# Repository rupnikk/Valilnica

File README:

KALILNIK

Urban Rupnik
Zadlog 42, 5274 Črni Vrh
Start: 6. 6. 2016

Navodila za git:
git add . -Af
git commit -am "bla"

Verzija 1.1: 6. 6. 2016
Komentarji k shemi:
	LCD: 	- potenciometer za nastavljanje svetlosti, 
			- R/W = GND => se samo piše v spomin LCD-ja

	Izhodi:	- Luci:		-180 omski upor za nastavitev napetosti, ki 					mora biti na triacu in zagotovitev odprtja 						triaca.
						- 2.4 ohm + 0.2uF -> Snubber za optospojnik
						- 39 ohm + 0.05uF -> Snubber za induktivno breme
			- Grelec:	- brez Snubberjev zato ker je omsko breme

	Tipke: 	- paralelni upor -> pull-up upor (cca. 10k)
			- serijski upor -> ko je pin nastavljen kot vhod in je tipka pritisnjena (nizko stanje na vhodu) skozi tranzistor steče tok, ki je zaradi velike Ugs prevelik in lahko uniči pin. (cca. 220 ohm)

	Enkoder: - 10k pull-up upor, in 10k + 0.1uF C za filter

	MCU: 	- Potrebujemo najmanj 21 digitalnih I/O pinov => najmanjši tak je 32 pinski.
			- ne potrebujemo veliko spomina, niti procesorske moči, tako da bi se odločil za ATtiny88 NIMA možnosti za zunanji kristalni oscilator!!!!!!!!
		- Izbral sem ATMEGA32M1-AU

	Switcher: -http://si.farnell.com/infineon/ifx91041ej-v50/dc-dc-conv-buck-370khz-soic-8/dp/2432504

			- blokirni kondenzatorji cca. 2.2u in 100n

			- pi filter: (1/10*f0) f0=1/(2*pi*sqrt(L*C))

	konektorji: signalni: -jst xhp
			močnostni: 5.08 mm bom potem zbral

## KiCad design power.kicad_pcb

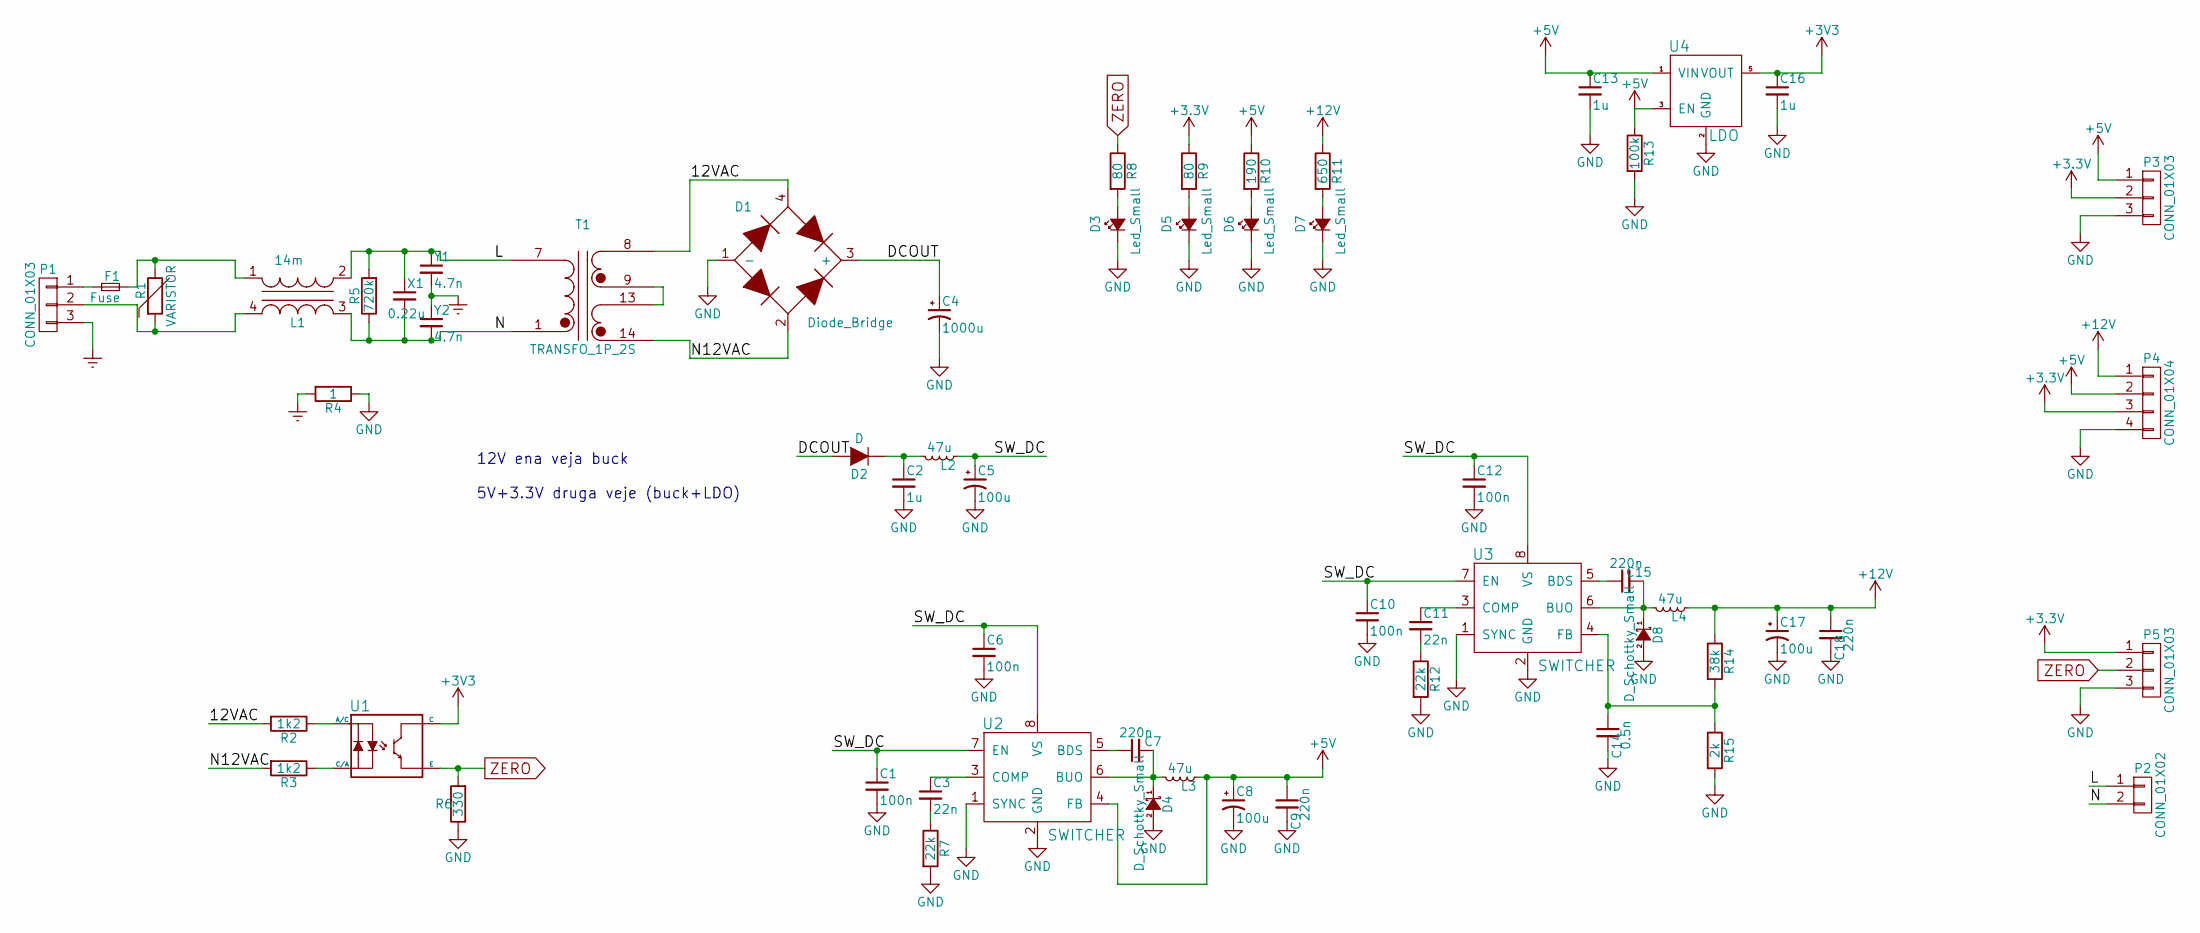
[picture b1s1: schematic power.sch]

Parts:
C1, C6, C10, C12: 100n; C_0603_HandSoldering
C2: 1u; R_0603_HandSoldering
C3, C11: 22n; C_0603_HandSoldering
C4: 1000u; C_13_21_5; Farnell number 9451323
C5, C8, C17: 100u; C_Radial_D6.3_L11.2_P2.5; Farnell number 9451080
C7, C9, C15, C18: 220n; C_0603_HandSoldering
C13, C16: 1u; C_0603_HandSoldering
C14: 0.5n; C_0603_HandSoldering
D1: Diode_Bridge; CIRC_BRIDGE_RECT
D2: D; SOD323F; Farnell number 1757770
D3: Led_Small; R_0603_HandSoldering; Farnell number 2463988
D4, D8: D_Schottky_Small; SOD323F; Farnell number 2575120
D5, D6, D7: Led_Small; R_0603_HandSoldering; Farnell number 2426215
F1: Fuse; Fuseholder_Fuse_5x20; Farnell number 1271632
L1: 14m; FILTER_SU9V; Farnell number 2364377
L2, L3, L4: 47u; TYS4018470M-10; Farnell number 2292522
P1: CONN_01X03; CONN_3x1x5.08; Farnell number 2008020
P2: CONN_01X02; CONN_2x1x5.08
P3, P5: CONN_01X03; CONN_3x1x2.54
P4: CONN_01X04; CONN_4x1x2.54
R1: VARISTOR; VARISTOR_MOV-14D431KTR; Farnell number 2250941
R2, R3: 1k2; CFR25; Farnell number 2329708
R4: 1; R_0805_HandSoldering
R5: 720k; CFR25; Farnell number 2329704
R6: 330; R_0603_HandSoldering
R7, R12: 22k; R_0603_HandSoldering
R8, R9: 80; R_0603_HandSoldering
R10: 190; R_0603_HandSoldering
R11: 650; R_0603_HandSoldering
R13: 100k; R_0603_HandSoldering
R14: 38k; R_0603_HandSoldering
R15: 2k; R_0603_HandSoldering
T1: TRANSFO_1P_2S; TRAFO_17_89_1314; Farnell number 1214618
U1: TRIAC_OPTOCOUPLER_2D+CE; SFH620-SMD_4pin; Farnell number 1469585
U2: SWITCHER; SOIC-8-N; Farnell number 2432504
U3: SWITCHER; SOIC-8-N; Farnell number 2480506
U4: LDO; SOT23-5; Farnell number 2363036
X1: 0.22u; X2_B32922; Farnell number 1112842
Y1, Y2: 4.7n; Y2_L20C7H; Farnell number 2576709

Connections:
+5V: C8.1, C9.1, C13.1, L3.1, P3.1, P4.2, R10.1, R13.1, U2.4 (FB), U4.1 (VIN), U4.3 (EN)
+12V: C17.1, C18.1, L4.1, P4.1, R11.1, R14.1
/12VAC: D1.4, R2.2, T1.8 (SB)
/DCOUT: C4.1, D1.3 (+), D2.2 (A)
/L: L1.2 (AB), P2.1, R5.2, T1.7 (AA), X1.1, Y1.1
/N: L1.3 (SA), P2.2, R5.1, T1.1 (AB), X1.2, Y2.2
/N12VAC: D1.2, R3.2, T1.14 (SC)
/SW_DC: C1.1, C5.1, C6.1, C10.1, C12.1, L2.1, U2.7 (EN), U2.8 (VS), U3.7 (EN), U3.8 (VS)
Earth: P1.3, R4.2, Y1.2, Y2.1
GND: C1.2, C2.2, C4.2, C5.2, C6.2, C8.2, C9.2, C10.2, C12.2, C13.2, C14.2, C16.2, C17.2, C18.2, D1.1 (-), D3.1 (K), D4.2 (A), D5.1 (K), D6.1 (K), D7.1 (K), D8.2 (A), P3.3, P4.4, P5.3, R4.1, R6.1, R7.2, R12.2, R13.2, R15.2, U2.1 (SYNC), U2.2 (GND), U3.1 (SYNC), U3.2 (GND), U4.2 (GND)
unnamed: C2.1, D2.1 (K), L2.2
unnamed: C3.1, U2.3 (COMP)
unnamed: C3.2, R7.1
unnamed: C7.1, U2.5 (BDS)
unnamed: C7.2, D4.1 (K), L3.2, U2.6 (BUO)
unnamed: C11.1, U3.3 (COMP)
unnamed: C11.2, R12.1
unnamed: C14.1, R14.2, R15.1, U3.4 (FB)
unnamed: C15.1, U3.5 (BDS)
unnamed: C15.2, D8.1 (K), L4.2, U3.6 (BUO)
unnamed: D3.2 (A), R8.2
unnamed: D5.2 (A), R9.2
unnamed: D6.2 (A), R10.2
unnamed: D7.2 (A), R11.2
unnamed: F1.1, P1.1
unnamed: F1.2, L1.1 (AA), R1.1
unnamed: L1.4 (SB), P1.2, R1.2
unnamed: R2.1, U1.1 (A/C)
unnamed: R3.1, U1.2 (C/A)
unnamed: T1.9 (SA), T1.13 (SD)
ZERO: P5.2, R6.2, R8.1, U1.3 (E)

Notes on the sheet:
12V ena veja buck 5V+3.3V druga veje (buck+LDO)

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
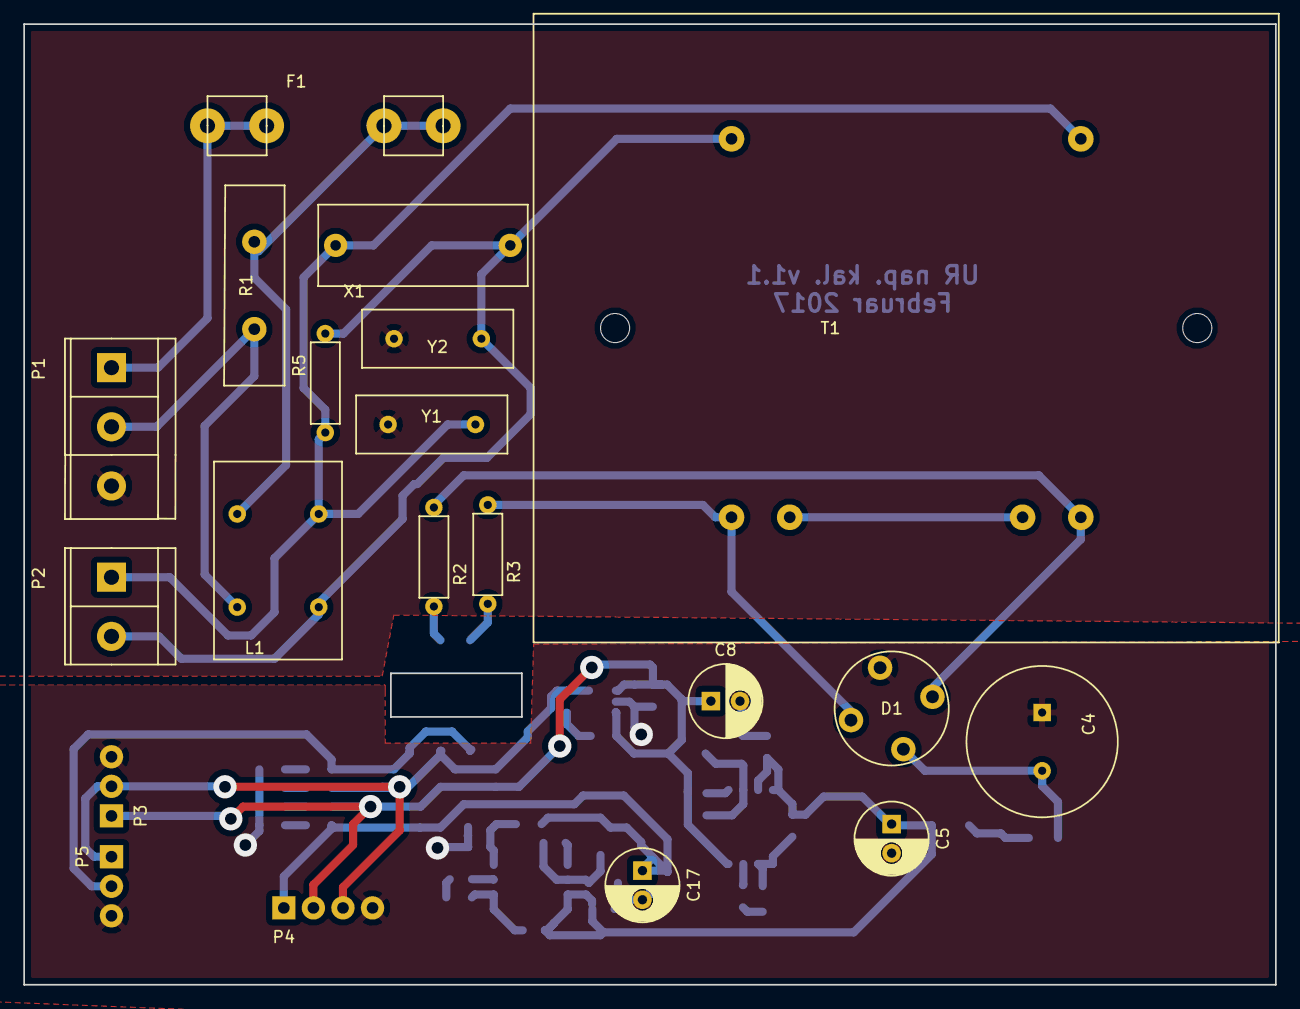
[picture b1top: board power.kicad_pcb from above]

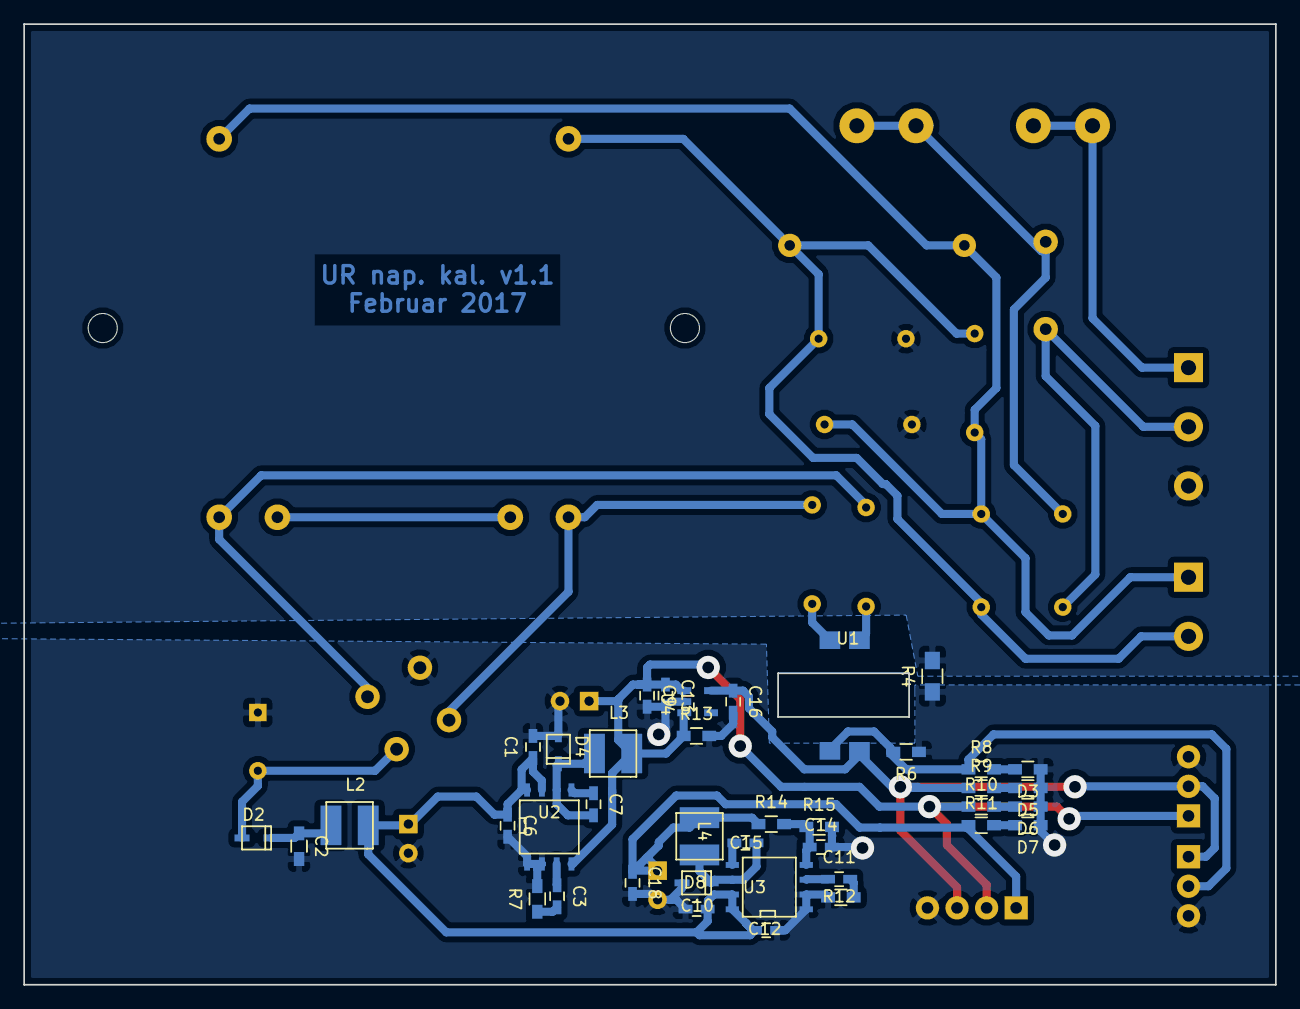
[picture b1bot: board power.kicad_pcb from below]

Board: 2 copper layers, 107.5 x 82.5 mm, 59 parts (39 on the bottom side), 32 nets.

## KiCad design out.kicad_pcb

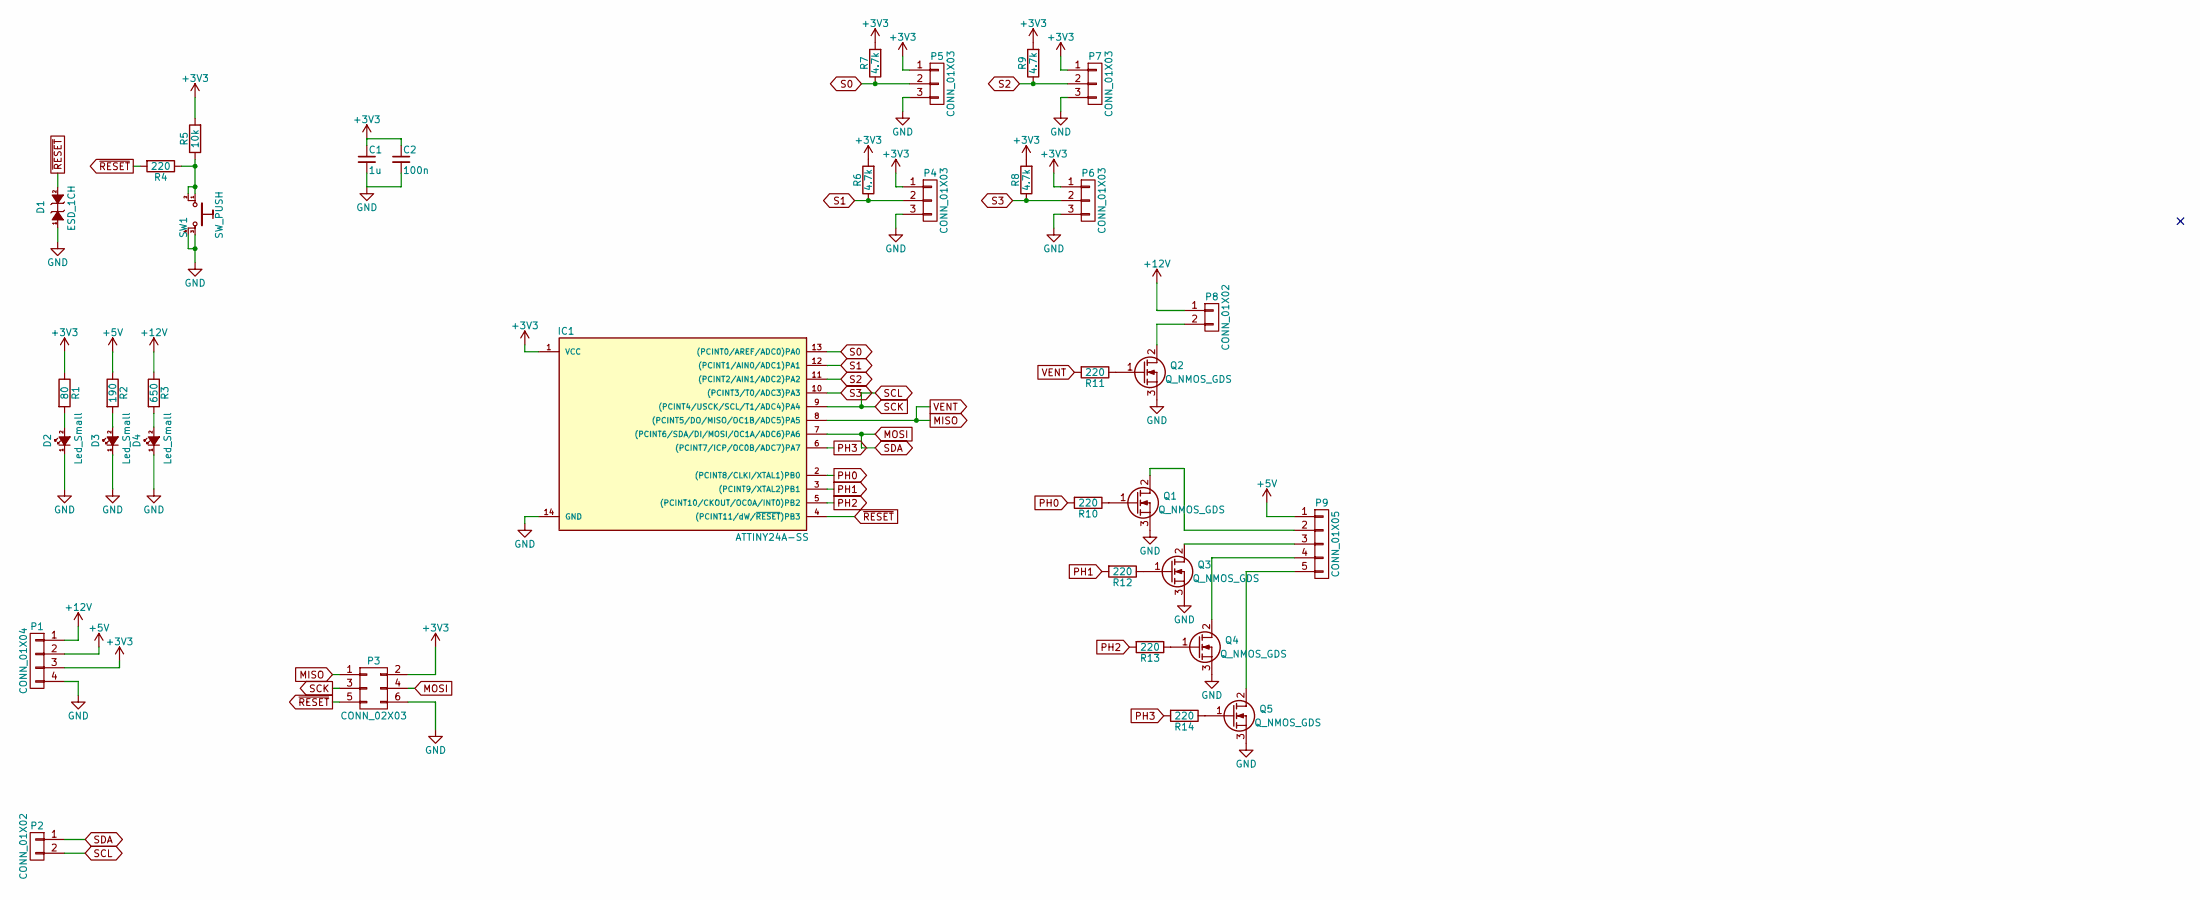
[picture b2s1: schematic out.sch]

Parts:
C1: 1u; C_0603_HandSoldering
C2: 100n; C_0603_HandSoldering
D1: ESD_1CH; SOD323F; Farnell number 8737517
D2, D3, D4: Led_Small; R_0603_HandSoldering
IC1: ATTINY24A-SS; SOIC-14_3.9x8.7mm_Pitch1.27mm
P1: CONN_01X04; CONN_4x1x2.54
P2: CONN_01X02; CONN_2x1x2.54
P3: CONN_02X03; IDC_Header_Straight_6pins
P4, P5, P6, P7: CONN_01X03; CONN_3x1x2.54
P8: CONN_01X02; CONN_2x1x5.08
P9: CONN_01X05; CONN_5x1x2.54
Q1, Q2, Q3, Q4, Q5: Q_NMOS_GDS; SOT89-3_Housing_Handsoldering_123; Farnell number 1834055
R1: 80; R_0603_HandSoldering
R2: 190; R_0603_HandSoldering
R3: 650; R_0603_HandSoldering
R4, R10, R11, R12, R13, R14: 220; R_0603_HandSoldering
R5: 10k; R_0603_HandSoldering
R6, R7, R8, R9: 4.7k; R_0603_HandSoldering
SW1: SW_PUSH; TACTILE_SWTICH_4PIN

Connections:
+3V3: C1.1, C2.1, IC1.1 (VCC), P1.3, P3.2, P4.1, P5.1, P6.1, P7.1, R1.1, R5.2, R6.2, R7.2, R8.2, R9.2
+5V: P1.2, P9.1, R2.1
+12V: P1.1, P8.1, R3.1
GND: C1.2, C2.2, D1.1 (K), D2.1 (K), D3.1 (K), D4.1 (K), IC1.14 (GND), P1.4, P3.6, P4.3, P5.3, P6.3, P7.3, Q1.3 (S), Q2.3 (S), Q3.3 (S), Q4.3 (S), Q5.3 (S), SW1.3, SW1.4
MISO: IC1.8 ((PCINT5/DO/MISO/OC1B/ADC5)PA5), P3.1, R11.2
MOSI: IC1.7 ((PCINT6/SDA/DI/MOSI/OC1A/ADC6)PA6), P2.1, P3.4
unnamed: D2.2 (A), R1.2
unnamed: D3.2 (A), R2.2
unnamed: D4.2 (A), R3.2
unnamed: P8.2, Q2.2 (D)
unnamed: P9.2, Q1.2 (D)
unnamed: P9.3, Q3.2 (D)
unnamed: P9.4, Q4.2 (D)
unnamed: P9.5, Q5.2 (D)
unnamed: Q1.1 (G), R10.1
unnamed: Q2.1 (G), R11.1
unnamed: Q3.1 (G), R12.1
unnamed: Q4.1 (G), R13.1
unnamed: Q5.1 (G), R14.1
unnamed: R4.1, R5.1, SW1.1, SW1.2
PH0: IC1.2 ((PCINT8/CLKI/XTAL1)PB0), R10.2
PH1: IC1.3 ((PCINT9/XTAL2)PB1), R12.2
PH2: IC1.5 ((PCINT10/CKOUT/OC0A/INT0)PB2), R13.2
PH3: IC1.6 ((PCINT7/ICP/OC0B/ADC7)PA7), R14.2
S0: IC1.13 ((PCINT0/AREF/ADC0)PA0), P5.2, R7.1
S1: IC1.12 ((PCINT1/AIN0/ADC1)PA1), P4.2, R6.1
S2: IC1.11 ((PCINT2/AIN1/ADC2)PA2), P7.2, R9.1
S3: IC1.10 ((PCINT3/T0/ADC3)PA3), P6.2, R8.1
SCK: IC1.9 ((PCINT4/USCK/SCL/T1/ADC4)PA4), P2.2, P3.3
~RESET: D1.2 (A), IC1.4 ((PCINT11/dW/~RESET~)PB3), P3.5, R4.2

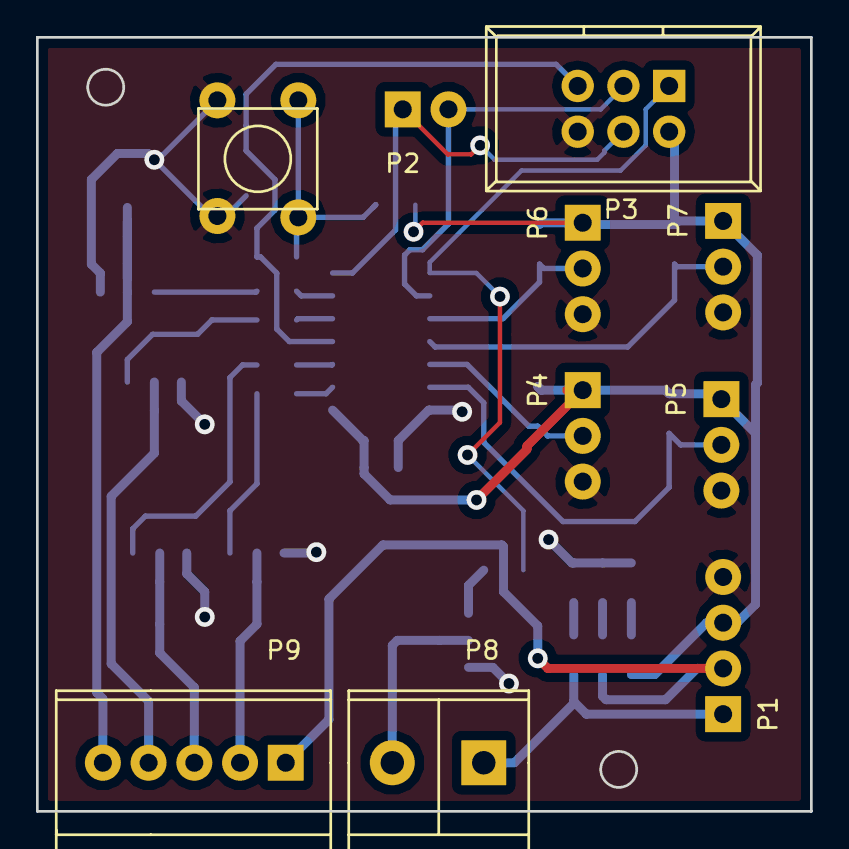
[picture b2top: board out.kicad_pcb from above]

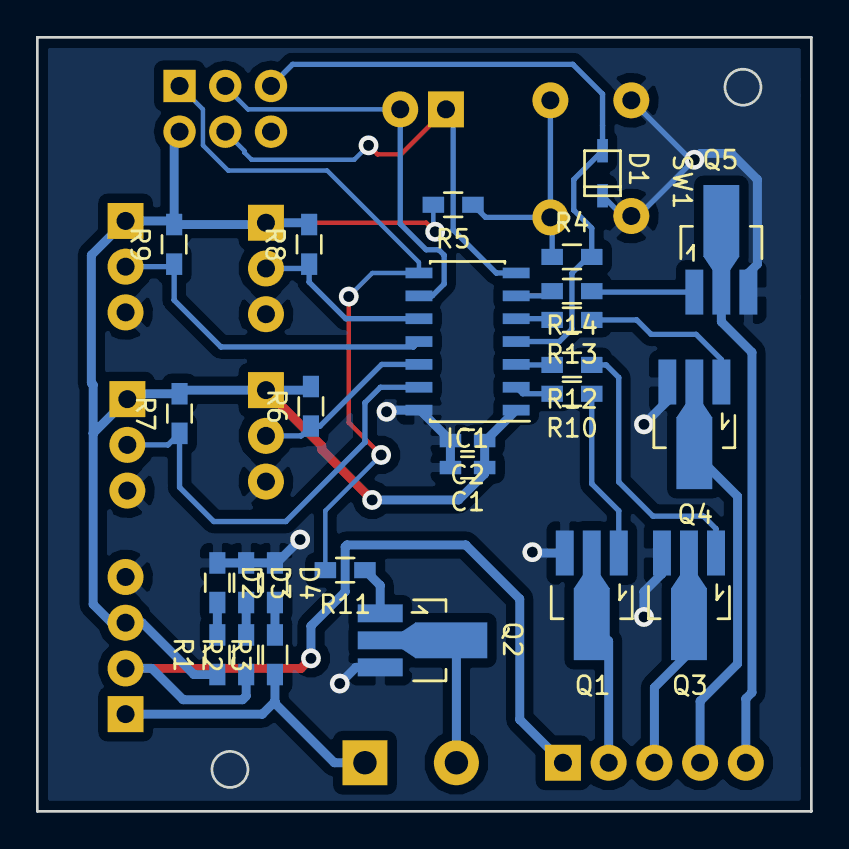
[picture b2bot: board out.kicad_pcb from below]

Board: 2 copper layers, 43.0 x 43.0 mm, 36 parts (27 on the bottom side), 30 nets.

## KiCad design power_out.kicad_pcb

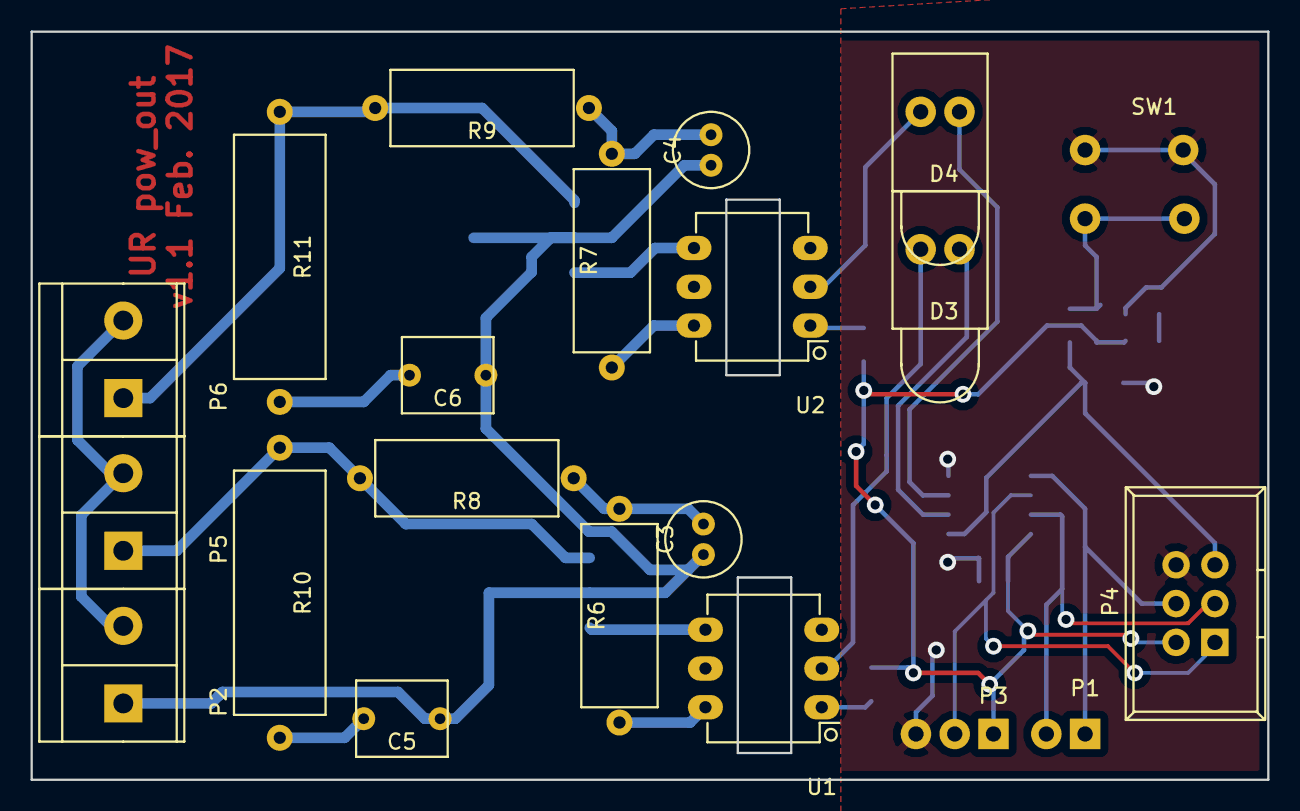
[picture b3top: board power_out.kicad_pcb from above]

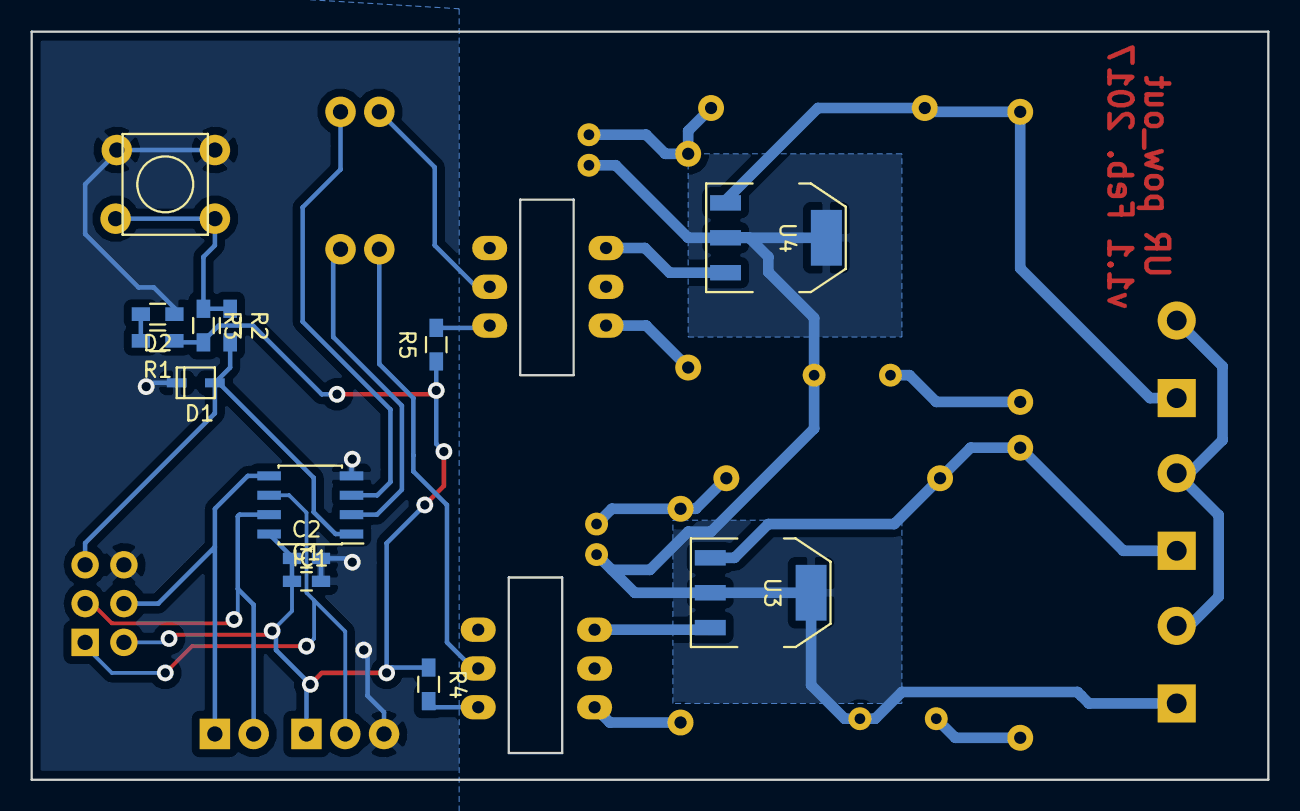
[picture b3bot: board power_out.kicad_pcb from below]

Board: 2 copper layers, 81.0 x 49.0 mm, 33 parts (12 on the bottom side), 26 nets.

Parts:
C1: 1u; C_0603_HandSoldering
C2: 100n; C_0603_HandSoldering
C3, C4: 200n; C_5x11_2
C5, C6: 50n 500V+; c_60pF
D1: ESD_1CH; SOD323F
D2: Led_Small; R_0603_HandSoldering
D3, D4: Led_Small; LED_0_1inch
IC1: ATTINY85-S; SOIC-8_3.9x4.9mm_Pitch1.27mm
P1: CONN_01X02; CONN_2x1x2.54
P2, P5, P6: CONN_01X02; CONN_2x1x5.08
P3: CONN_01X03; CONN_3x1x2.54
P4: CONN_02X03; IDC_Header_Straight_6pins
R1: R; R_0603_HandSoldering
R2, R4, R5: 220; R_0603_HandSoldering
R3: 10k; R_0603_HandSoldering
R6, R7: 180; CFR100
R8, R9: 2k4; CFR100
R10, R11: 39 2W; CFR200
SW1: SW_PUSH; TACTILE_SWTICH_4PIN
U1, U2: TRIAC_OPTOCOUPLER; DIP-6_W7.62mm_LongPads
U3, U4: TRIAC; SOT-223_THERMAL

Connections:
+3V3: C1.1, C2.1, IC1.8, P3.1, P4.2, R1.1, R3.2, R4.1, R5.1
/L: C3.2, C4.2, C5.2, C6.2, P2.1, U3.2, U4.2
/N: P2.2, P5.2, P6.2
GND: C1.2, C2.2, D1.1, D2.1, IC1.4, P3.3, P4.6, SW1.3, SW1.4
GRELEC: D3.1, IC1.2
LUC: D4.1, IC1.3
MISO: IC1.6, P3.2, P4.1
MOSI: IC1.5, P1.1, P4.4
unnamed: C3.1, R6.1, R8.2
unnamed: C4.1, R7.1, R9.2
unnamed: C5.1, R10.1
unnamed: C6.1, R11.1
unnamed: D2.2, R1.2
unnamed: D3.2, U1.2
unnamed: D4.2, U2.2
unnamed: P5.1, R8.1, R10.2, U3.1
unnamed: P6.1, R9.1, R11.2, U4.1
unnamed: R2.1, R3.1, SW1.1, SW1.2
unnamed: R4.2, U1.1
unnamed: R5.2, U2.1
unnamed: R6.2, U1.6
unnamed: R7.2, U2.6
unnamed: U1.4, U3.3
unnamed: U2.4, U4.3
SCK: IC1.7, P1.2, P4.3
~RESET: D1.2, IC1.1, P4.5, R2.2

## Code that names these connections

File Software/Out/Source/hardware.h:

/*
 * hardware.h
 *
 *  Created on: 16. jan. 2017
 *      Author: Urban Rupnik
 *      City: Zadlog 42
 */

#include <avr/io.h>
#include <util/delay.h>


#ifndef HARDWARE_H_
#define HARDWARE_H_

	#define DDR_USI			DDRA
	#define PORT_USI		PORTA
	#define PIN_USI			PINA
	#define PORT_USI_SDA	PA6
	#define PORT_USI_SCL	PA4
	#define PIN_USI_SDA		PINA6
	#define PIN_USI_SCL		PINA4


	#define VENT 			PB3
	#define VENT_PORT		PORTB
	#define VENT_DIR_PORT	DDRB

	#define PH0 			PB0
	#define PH0_PORT		PORTB
	#define PH0_DIR_PORT	DDRB

	#define PH1 			PB1
	#define PH1_PORT		PORTB
	#define PH1_DIR_PORT	DDRB

	#define PH2 			PB2
	#define PH2_PORT		PORTB
	#define PH2_DIR_PORT	DDRB

	#define PH3 			PA7
	#define PH3_PORT		PORTA
	#define PH3_DIR_PORT	DDRA

	#define S0				PA0
	#define S0_PORT 		PORTA
	#define S0_DIR_PORT		DDRA
	#define S0_VALUE_REG	PINA

	#define S1				PA1
	#define S1_PORT 		PORTA
	#define S1_DIR_PORT		DDRA
	#define S1_VALUE_REG	PINA

	#define S2				PA2
	#define S2_PORT 		PORTA
	#define S2_DIR_PORT		DDRA
	#define S2_VALUE_REG	PINA

	#define S3				PA3
	#define S3_PORT 		PORTA
	#define S3_DIR_PORT		DDRA
	#define S3_VALUE_REG	PINA


#endif /* HARDWARE_H_ */

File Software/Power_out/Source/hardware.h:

/*
 * hardware.h
 *
 *  Created on: 16. jan. 2017
 *      Author: Urban Rupnik
 *      City: Zadlog 42
 */

#include <avr/io.h>
#include <util/delay.h>


#ifndef HARDWARE_H_
#define HARDWARE_H_

	#define DDR_USI			DDRB
	#define PORT_USI		PORTB
	#define PIN_USI			PINB
	#define PORT_USI_SDA	PB0
	#define PORT_USI_SCL	PB2
	#define PIN_USI_SDA		PINB0
	#define PIN_USI_SCL		PINB2


	#define GRELEC 			PB3
	#define GRELEC_PORT		PORTB
	#define GRELEC_DIR_PORT	DDRB

	#define LUC 			PB4
	#define LUC_PORT		PORTB
	#define LUC_DIR_PORT	DDRB

	#define ZERO			PB1
	#define ZERO_PORT		PORTB
	#define ZERO_DIR_PORT	DDRB
	#define ZERO_VALUE_REG 	PINB
	#define ZERO_PCINT		PCINT1



#endif /* HARDWARE_H_ */

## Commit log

2017-06-28 prva
2017-06-29 recmo
2017-07-06 mora delat pa verjetno ne bo
